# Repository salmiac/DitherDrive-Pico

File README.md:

# Proportional Valve Controller / Proportionaaliventtiilin Ohjain (RP2040)

This document contains instructions in both Finnish and English.
Tämä dokumentti sisältää ohjeet sekä suomeksi että englanniksi.

---

## 🇫🇮 Suomenkielinen dokumentaatio

### 1. Yleiskatsaus
Tämä projekti kuvaa edullisen, suljetun säätöpiirin (closed-loop) proportionaaliventtiiliohjaimen, joka on rakennettu Raspberry Pi Pico (RP2040) -mikrokontrollerin ympärille. Ohjain on suunniteltu erityisesti 24 V raskaan kaluston järjestelmiin (esim. Kawasakin SKC5P-14A -pumppuventtiilit).

**Pääominaisuudet:**
- **Virtatakaisinkytkentä (Closed-Loop):** Pitää venttiilin virran ja karan asennon vakaana kelan lämpötilavaihteluista huolimatta (PI-säätö INA219-sensorilla).
- **Laitteistotason Dither (muokattava):** Picon erittäin tarkan PWM-generaattorin avulla tuotettu matalataajuinen dither-signaali, joka estää venttiilin karan takertelun (stiction).
- **Tehokas laskentakyky:** RP2040:n dual-core ARM Cortex-M0+ -arkkitehtuuri tarjoaa riittävästi tehoa reaaliaikaiseen PI-säätöön, ditherin laskentaan ja sarjaporttivianmääritykseen (debugging).
- **Häiriösuojaus:** Suunniteltu sietämään työkoneiden jännitepiikkejä (Load dump) TVS- ja Zener-suojadiodeilla.

### 2. Komponenttilistaus (BOM)

| Komponentti | Malli / Tyyppi | Käyttötarkoitus | Huomautus |
| :--- | :--- | :--- | :--- |
| **Mikrokontrolleri** | Raspberry Pi Pico (RP2040) | Äly, PWM ja PI-säätö. Sisältää USB-ohjelmoinnin ja sarjaporttidebuggauksen. | Voi käyttää myös Pico W -mallia. |
| **Virtamittaus** | INA219 (I2C-moduuli) | Mittaa kelan läpi kulkevan virran reaaliajassa. | Käyttöjännite 3.3V Picon linjasta. |
| **DC/DC-muunnin** | Traco TSR 1-2450 tai Recom R-785.0 | Laskee työkoneen 24V jännitteen häviöttömästi 5 volttiin (Picon VSYS-pinnille). | Minimissään 500mA versio. |
| **Gate Driver** | TC4420 (tai MIC4427 / TC4427) | Sovittaa Picon 3.3V GPIO-signaalin MOSFETin ohjaushilalle (Gate) riittävällä jännitteellä ja virralla. | Erittäin tärkeä MOSFETin nopealle toiminnalle. |
| **MOSFET** | IRF540N tai IRL540 | Kytkee 24V jännitettä venttiilin kelalle. | IRL540 on logic-level-malli ja aukeaa matalammalla jännitteellä. |
| **Vapaakytkintädiodi** | UF5404 tai UF5408 | Nopea diodi magneettikentän purkamiseen (Fast Flyback). | UF5408 kestää korkeampaa jännitettä (1000V). |
| **Zener-diodi** | 1N5359B (24V, 5W) | Vauhdittaa kelan purkautumista yhdessä vapaakytkintädiodin kanssa. | Nopeuttaa karan palautumista. |
| **TVS-diodi** | 1.5KE36A tai 1.5KE36CA | Tappaa 24V järjestelmän yli 36V jännitepiikit. | Suojaa koko kytkentää työkoneen kuormaiskuilta. |
| **Potentiometri** | 10 kΩ (Lineaarinen) | Käyttöliittymä tavoitevirran asettamiseen (150–700 mA). | Kytketään 3.3 V jännitteeseen. |

### 3. Raspberry Pi Pico Kytkennät (Pinout)

- **VSYS (Pin 39):** Virtalähteen 5V sisääntulo (Traco/Recom DC/DC-muuntimelta).
- **GND (Pin 38 tai mikä tahansa GND):** Yhteinen maapiste (Työkoneen runko / akun miinus).
- **3.3V OUT (Pin 36):** Syöttää 3.3 V jännitteen INA219-moduulille sekä 10 kΩ potentiometrin yläpäähän.
- **GP4 / SDA (Pin 6):** INA219-moduulin SDA-pinni.
- **GP5 / SCL (Pin 7):** INA219-moduulin SCL-pinni.
- **GP26 / ADC0 (Pin 31):** Kytketään potentiometrin liukuun (suositellaan 1 kΩ sarjavastusta ja 100 nF kondensaattoria maihin RC-suotimeksi).
- **GP15 / PWM Out (Pin 20):** Kytketään TC4420 Gate Driverin IN-pinniin.

### 4. Kytkentäkaavio (Wiring Diagram)

```mermaid
graph TD
    classDef mcu fill:#008080,stroke:#004d4d,stroke-width:2px,color:#fff;
    classDef power fill:#744210,stroke:#d69e2e,stroke-width:2px,color:#fff;
    classDef sensor fill:#22543d,stroke:#38a169,stroke-width:2px,color:#fff;
    classDef driver fill:#2c5282,stroke:#4299e1,stroke-width:2px,color:#fff;
    classDef discrete fill:#4a5568,stroke:#718096,stroke-width:1px,color:#fff;
    classDef load fill:#742a2a,stroke:#e53e3e,stroke-width:2px,color:#fff;

    subgraph Power_Supply ["Power Supply & Protection / Virtalähde & Suojaus"]
        V24["24V Power Input"]:::power
        TVS["TVS Diode 1.5KE36A"]:::discrete
        Traco["DC/DC Converter (5V Out)"]:::power
        V5["5V DC/DC Output"]:::power
        GND["System Ground (GND)"]:::power
    end

    subgraph Control_Logic ["Control Logic / Ohjauslogiikka"]
        Pico["Raspberry Pi Pico"]:::mcu
        Pot["Potentiometer 10k"]:::discrete
        RC_R["Resistor 1k"]:::discrete
        RC_C["Capacitor 100nF"]:::discrete
    end

    subgraph Sensing_Driving ["Current Sensing & Power Driver / Virtamittaus & Tehoaste"]
        INA["INA219 Current Sensor"]:::sensor
        Driver["Gate Driver TC4420"]:::driver
        MOSFET["MOSFET IRF540N"]:::discrete
    end

    subgraph Actuator ["Load / Valve Coil (Kuorma / Venttiilin Kela)"]
        Coil["Proportional Valve Coil"]:::load
        UF5404["Flyback Diode UF5404"]:::discrete
        Zener["Zener Diode 1N5359B (24V)"]:::discrete
    end

    %% Power distribution
    V24 --> TVS
    TVS --> GND
    V24 -->|"Vin (Pin 1)"| Traco
    Traco -->|"GND (Pin 2)"| GND
    Traco -->|"Vout (Pin 3)"| V5

    %% Logic power
    V5 -->|"VSYS (Pin 39)"| Pico
    V5 -->|"VDD"| Driver
    Pico -->|"3.3V OUT (Pin 36) -> VCC"| INA
    Pico -->|"3.3V OUT (Pin 36) -> VCC"| Pot

    %% Analog setpoint input
    Pot -->|"Wiper"| RC_R
    RC_R --> RC_C
    RC_C --> GND
    RC_R -->|"GP26 (ADC0 / Pin 31)"| Pico

    %% Control lines
    Pico -- "GP4 (SDA) -> SDA" --> INA
    Pico -- "GP5 (SCL) -> SCL" --> INA
    Pico -- "GP15 (PWM / Pin 20) -> IN" --> Driver

    %% Load power path
    V24 -->|"VIN+"| INA
    INA -->|"VIN-"| Coil
    Coil -->|"Drain"| MOSFET
    MOSFET -->|"Source"| GND
    Driver -->|"OUT -> Gate"| MOSFET

    %% Fast Flyback path (anti-parallel to Coil)
    Coil-.-|Node 2: Drain| UF5404
    UF5404-.-|Cathode to Cathode| Zener
    Zener-.-|Anode to Node 1: VIN-| Coil

    %% GND references
    Pico ---|"GND (Pin 38)"| GND
    Pot ---|"GND"| GND
    INA ---|"GND"| GND
    Driver ---|"GND"| GND
    MOSFET ---|"Source"| GND
```

### 5. Ohjelmointi (PlatformIO)
Projekti on määritelty PlatformIO-projektiksi (juuresta löytyy `platformio.ini`), mikä on suositeltava kehitysympäristö. Pico on helppo ohjelmoida USB-liitännän kautta ilman ulkoisia ohjelmointilaitteita.

1. Avaa projektikansio VS Codessa, jossa on PlatformIO-laajennus.
2. PlatformIO käyttää `platformio.ini`-tiedostoa, johon on asetettu seuraavat asetukset Picolle (tämä lataa tarvittavat kirjastot automaattisesti):

```ini
[env:pico]
platform = raspberrypi
board = pico
framework = arduino
lib_deps = adafruit/Adafruit INA219 @ ^1.2.1
```

**Latausohje:**
1. Kytke micro-USB-kaapeli tietokoneeseen.
2. Jos koodia ladataan ensimmäistä kertaa, pidä Picon **BOOTSEL**-painiketta painettuna samalla kun kytket USB-johdon. Pico ilmestyy tietokoneelle massamuistilaitteena (RPI-RP2).
3. Paina PlatformIO:sta **Upload** (nuoli-kuvake). Kääntäjä luo `.uf2`-tiedoston ja siirtää sen automaattisesti Picolle, minkä jälkeen laite käynnistyy uudelleen ja ajaa koodia.
4. Jatkossa voit käyttää tavallista sarjaportti-uploadia suoraan PlatformIO:sta ilman BOOTSEL-painikkeen painamista.

*(Vaihtoehtoisesti koodin voi myös kääntää perinteisessä Arduino IDE -ympäristössä kopioimalla `src/main.cpp`:n sisällön uuteen luonnokseen ja asentamalla "Adafruit INA219" -kirjaston sekä "Raspberry Pi Pico" -tuen Board Managerin kautta).*

---

## 🇬🇧 English Documentation

### 1. Overview
This project details a low-cost, closed-loop proportional valve controller built around a Raspberry Pi Pico (RP2040) microcontroller. The controller is specifically designed for 24V heavy machinery systems (e.g., Kawasaki SKC5P-14A pump valves).

**Key Features:**
- **Closed-Loop Current Control:** Maintains stable coil current and spool position regardless of coil temperature variations via a PI controller reading from an INA219 current sensor.
- **Hardware Dither (Configurable):** Utilizes the RP2040's highly flexible PWM block to generate low-frequency dither PWM, preventing spool stiction.
- **High Computational Power:** The dual-core ARM Cortex-M0+ architecture provides plenty of processing overhead for real-time PI loops, dither math, and detailed serial debugging logs.
- **Transient Protection:** Designed with TVS and Zener diodes to withstand harsh 24V load dumps commonly found in heavy machinery.

### 2. Bill of Materials (BOM)

| Component | Model / Type | Purpose | Notes |
| :--- | :--- | :--- | :--- |
| **Microcontroller** | Raspberry Pi Pico (RP2040) | Core logic, PWM, and PI control. Handles USB bootloader and serial logging. | Pico W (Wi-Fi/BT) can also be used. |
| **Current Sensor** | INA219 (I2C Module) | Reads the actual current passing through the valve coil in real time. | Powered by the Pico's 3.3V rail. |
| **DC/DC Converter** | Traco TSR 1-2450 or Recom R-785.0 | Steps down the 24V system voltage to a clean 5V logic supply (Pico VSYS pin). | Minimum 500mA version. |
| **Gate Driver** | TC4420 (or MIC4427 / TC4427) | Rapidly drives the MOSFET gate using 3.3V signals stepped up to VDD (5V/12V). | Critical for fast switching. |
| **MOSFET** | IRF540N or IRL540 | Switches the 24V load across the valve coil. | IRL540 is logic-level and opens at lower voltages. |
| **Flyback Diode** | UF5404 or UF5408 | Ultra-fast rectifier for magnetic field collapse (Fast Flyback). | UF5408 features a higher voltage rating (1000V). |
| **Zener Diode** | 1N5359B (24V, 5W) | Accelerates coil discharge when placed in series with the UF5404/UF5408. | Speeds up spool spring return. |
| **TVS Diode** | 1.5KE36A or 1.5KE36CA | Suppresses voltage spikes exceeding 36V in the 24V line. | Protects the circuit from load dumps. |
| **Potentiometer** | 10 kΩ (Linear) | User interface to set target current (150–700 mA). | Connected to the 3.3V rail. |

### 3. Raspberry Pi Pico Pin Configuration

- **VSYS (Pin 39):** 5V logic supply input (from Traco/Recom DC/DC converter).
- **GND (Pin 38 or any GND):** Common ground (Chassis / Battery negative).
- **3.3V OUT (Pin 36):** Supplies 3.3V power to the INA219 module and the high end of the 10 kΩ potentiometer.
- **GP4 / SDA (Pin 6):** Connected to INA219 SDA pin.
- **GP5 / SCL (Pin 7):** Connected to INA219 SCL pin.
- **GP26 / ADC0 (Pin 31):** Connected to the 10 kΩ potentiometer wiper (a 1 kΩ series resistor and 100 nF capacitor to GND is recommended as an RC filter).
- **GP15 / PWM Out (Pin 20):** Connected to the TC4420 Gate Driver IN pin.

### 4. Wiring Diagram (Kytkentäkaavio)
*(Refer to the Mermaid diagram in the Finnish section above for the full visual schematic).*

### 5. Programming (PlatformIO)
This project is configured as a PlatformIO project (featuring a `platformio.ini` in the root), which is the recommended development environment. The Pico is flashed directly via USB without external programmers.

1. Open the project folder in VS Code with the PlatformIO extension installed.
2. PlatformIO utilizes the `platformio.ini` configuration, which is set up for the Pico as follows (this will download library dependencies automatically):

```ini
[env:pico]
platform = raspberrypi
board = pico
framework = arduino
lib_deps = adafruit/Adafruit INA219 @ ^1.2.1
```

**Flashing Instructions:**
1. Connect a micro-USB cable to your PC.
2. If uploading for the first time, hold down the **BOOTSEL** button on the Pico while plugging in the USB cable. The Pico will mount as a USB storage drive (RPI-RP2).
3. Click **Upload** (arrow icon) in PlatformIO. The toolchain compiles the code to a `.uf2` file and writes it to the Pico. The board resets and starts executing the code immediately.
4. For subsequent uploads, you can use the standard USB serial upload from PlatformIO without holding down the BOOTSEL button.

*(Alternatively, the code can be built in the traditional Arduino IDE by copying the contents of `src/main.cpp` into a new sketch, and installing the "Adafruit INA219" library and "Raspberry Pi Pico" board support via the Board Manager).*

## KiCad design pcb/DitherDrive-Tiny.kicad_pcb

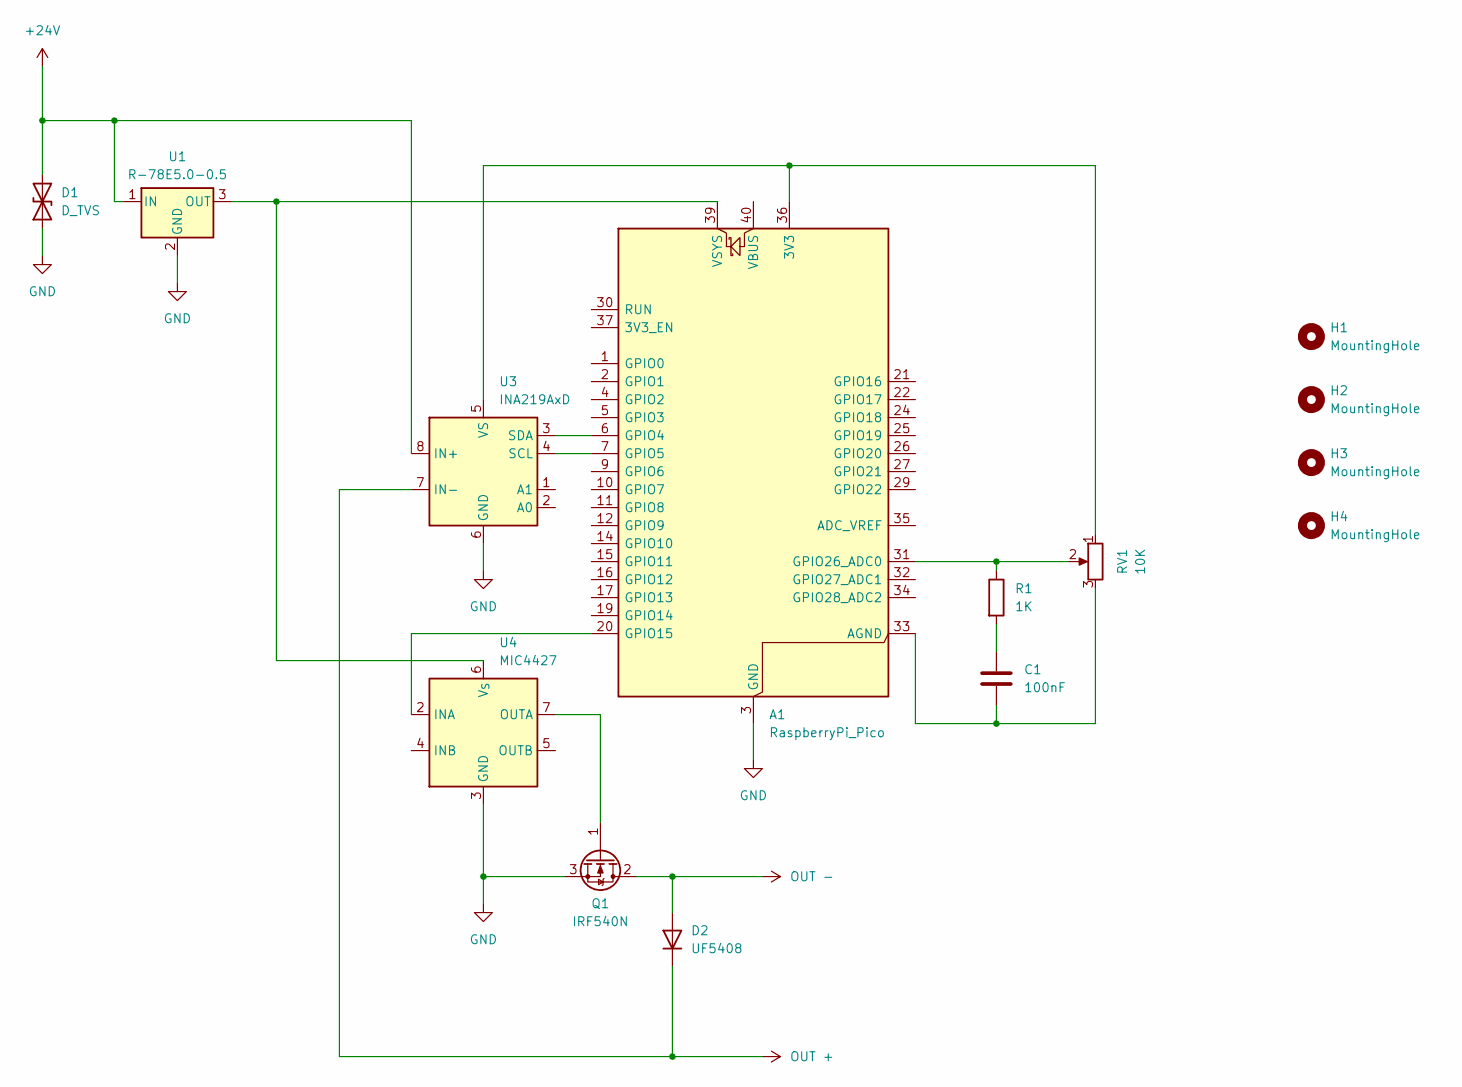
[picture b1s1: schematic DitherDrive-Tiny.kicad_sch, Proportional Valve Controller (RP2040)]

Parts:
A1: RaspberryPi_Pico; RaspberryPi_Pico_Common_Unspecified
C1: 100nF; C_Disc_D12.5mm_W5.0mm_P10.00mm
D1: D_TVS; D_DO-15_P15.24mm_Horizontal
D2: UF5408; D_DO-201AD_P15.24mm_Horizontal
H1, H2, H3, H4: MountingHole; MountingHole_4.5mm
Q1: IRF540N; TO-220-3_Vertical
R1: 1K; R_Axial_DIN0309_L9.0mm_D3.2mm_P15.24mm_Horizontal
RV1: 10K; Potentiometer_Piher_PC-16_Single_Horizontal
U1: R-78E5.0-0.5; Converter_DCDC_RECOM_R-78E-0.5_THT
U3: INA219AxD; INA219
U4: MIC4427; DIP-8_W7.62mm

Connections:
+24V: D1.2 (A2), U1.1 (IN), U3.8 (IN+)
GND: A1.3 (GND), A1.8 (GND), A1.13 (GND), A1.18 (GND), A1.23 (GND), A1.28 (GND), A1.38 (GND), D1.1 (A1), Q1.3 (S), U1.2 (GND), U3.6 (GND), U4.3 (GND)
unnamed: A1.36 (3V3), RV1.1, U3.5 (VS)
unnamed: A1.33 (AGND), C1.2, RV1.3
unnamed: A1.6 (GPIO4), U3.3 (SDA)
unnamed: A1.7 (GPIO5), U3.4 (SCL)
unnamed: A1.20 (GPIO15), U4.2 (INA)
unnamed: A1.31 (GPIO26_ADC0), R1.1, RV1.2
unnamed: A1.39 (VSYS), U1.3 (OUT), U4.6 (V_{S})
unnamed: C1.1, R1.2
unnamed: Q1.1 (G), U4.7 (OUTA)
OUT +: D2.1 (K), U3.7 (IN-)
OUT -: D2.2 (A), Q1.2 (D)

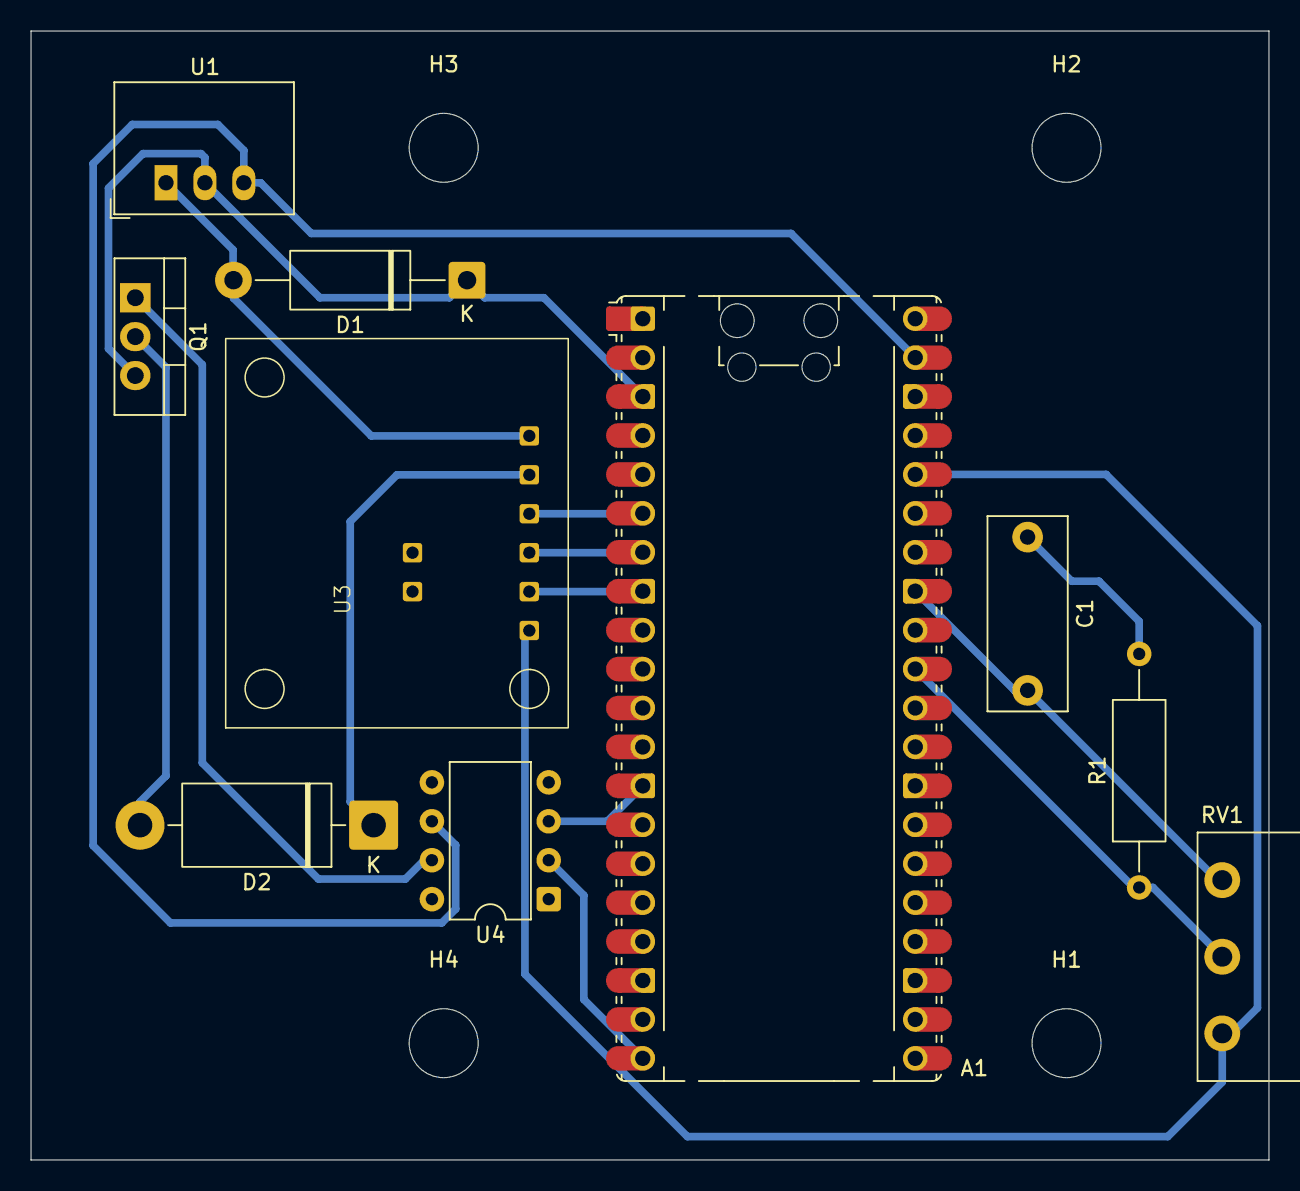
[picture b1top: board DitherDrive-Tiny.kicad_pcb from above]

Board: 2 copper layers, 80.8 x 73.7 mm, 14 parts (0 on the bottom side), 13 nets.

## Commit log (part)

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2026-06-14 init
